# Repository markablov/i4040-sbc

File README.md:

# i4040-sbc
Single-board computer design for Intel 4040 CPU

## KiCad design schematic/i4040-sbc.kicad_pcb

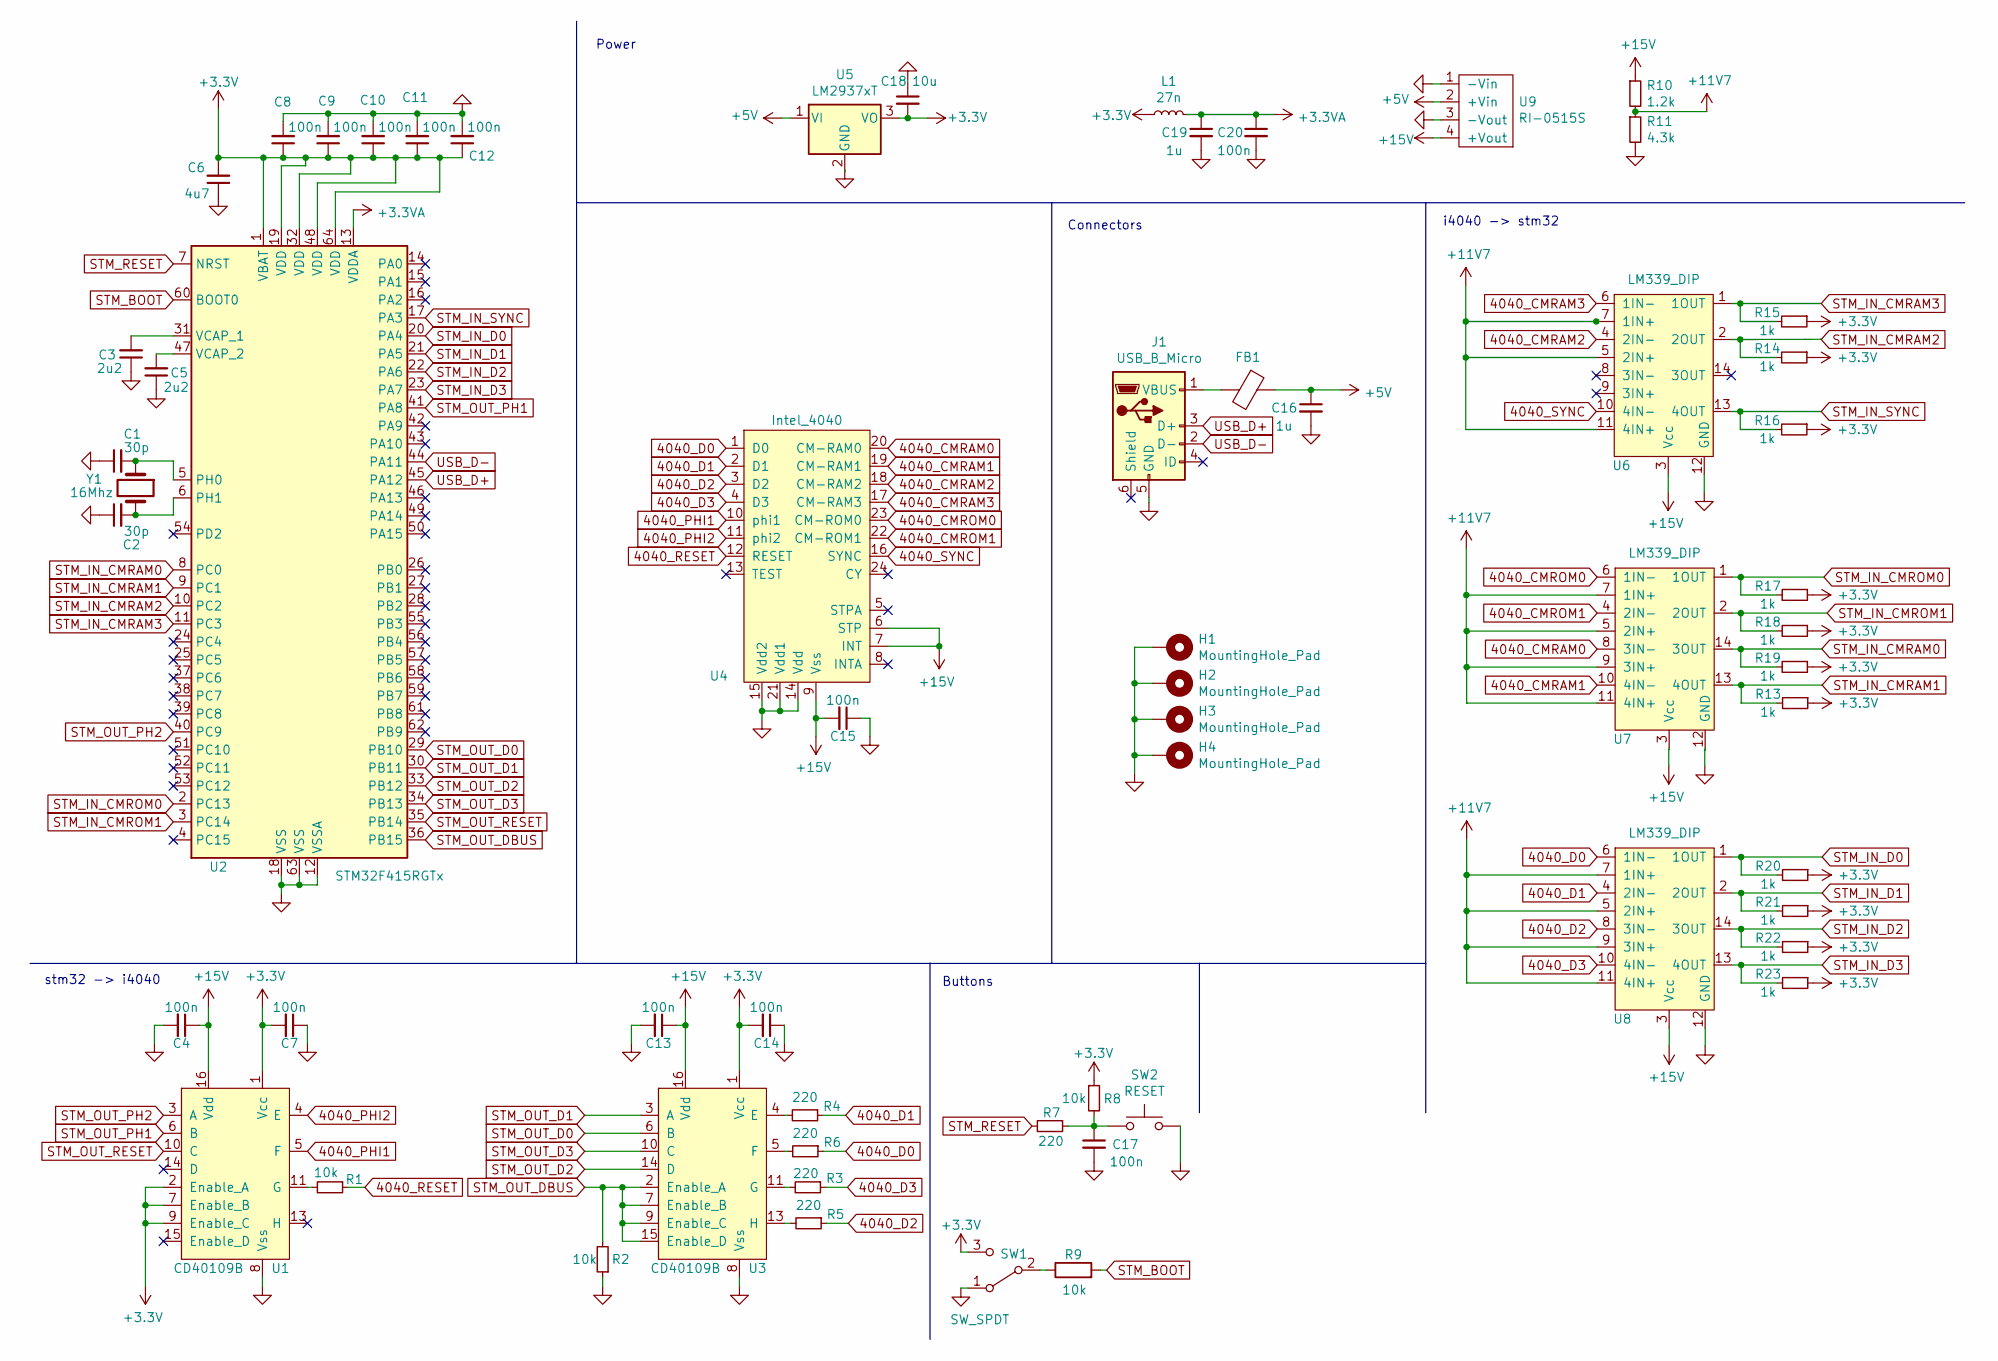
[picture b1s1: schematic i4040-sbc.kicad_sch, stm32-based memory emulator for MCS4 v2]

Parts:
C1, C2: 30p; C_Pillow_L5.6mm_W4mm_D5.6mm_P5.00mm
C3, C5: 2u2; C_Disc_D4.3mm_W1.9mm_P5.00mm
C4, C7, C13, C14, C15, C17, C20: 100n; C_Disc_D7mm_W5mm_P4.00mm
C6: 4u7; C_Disc_D4.3mm_W1.9mm_P5.00mm
C8, C9, C10, C11, C12: 100n; C_Disc_D4.7mm_W2.5mm_P5.00mm
C16, C19: 1u; C_Disc_D4.3mm_W1.9mm_P5.00mm
C18: 10u; C_Disc_D4.7mm_W2.5mm_P5.00mm
FB1: Ferrite_Bead; L_0402_1005Metric_Pad0.77x0.64mm_HandSolder
H1, H2, H3, H4: MountingHole_Pad; MountingHole_2.2mm_M2_Pad
J1: USB_B_Micro; USB_Micro-B_Amphenol_10104110_Horizontal
L1: 27n; L_0402_1005Metric_Pad0.77x0.64mm_HandSolder
R1, R2, R8, R9: 10k; R_Axial_DIN0207_L6.3mm_D2.5mm_P10.16mm_Horizontal
R3, R4, R5, R6, R7: 220; R_Axial_DIN0207_L6.3mm_D2.5mm_P10.16mm_Horizontal
R10: 1.2k; R_Axial_DIN0207_L6.3mm_D2.5mm_P10.16mm_Horizontal
R11: 4.3k; R_Axial_DIN0207_L6.3mm_D2.5mm_P10.16mm_Horizontal
R13, R14, R15, R16, R19, R20, R21, R22, R23: 1k; R_Axial_DIN0207_L6.3mm_D2.5mm_P10.16mm_Horizontal
R17, R18: 1k; R_Axial_DIN0414_L11.9mm_D4.5mm_P15.24mm_Horizontal
SW1: SW_SPDT; SW_Slide_1P2T_CK_OS102011MS2Q
SW2: RESET; SW_Tact_TS3601
U1, U3: CD40109B; SO-16_5.3x10.2mm_P1.27mm
U2: STM32F415RGTx; LQFP-64_10x10mm_P0.5mm
U4: Intel_4040; DIP-24_W15.24mm_Socket
U5: LM2937xT; TO-220-3_Vertical
U6, U7, U8: LM339_DIP; DIP-14_W7.62mm_Socket
U9: RI-0515S; Converter_DCDC_RECOM_R-78S-0.1_THT
Y1: 16Mhz; Crystal_HC49-U_Vertical

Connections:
4040_CMRAM0: U4.20 (CM-RAM0), U7.8 (3IN-)
4040_CMRAM1: U4.19 (CM-RAM1), U7.10 (4IN-)
4040_CMRAM2: U4.18 (CM-RAM2), U6.4 (2IN-)
4040_CMRAM3: U4.17 (CM-RAM3), U6.6 (1IN-)
4040_CMROM0: U4.23 (CM-ROM0), U7.6 (1IN-)
4040_CMROM1: U4.22 (CM-ROM1), U7.4 (2IN-)
4040_D0: R6.1, U4.1 (D0), U8.6 (1IN-)
4040_D1: R4.1, U4.2 (D1), U8.4 (2IN-)
4040_D2: R5.1, U4.3 (D2), U8.8 (3IN-)
4040_D3: R3.1, U4.4 (D3), U8.10 (4IN-)
4040_PHI1: U1.5 (F), U4.10 (phi1)
4040_PHI2: U1.4 (E), U4.11 (phi2)
4040_RESET: R1.1, U4.12 (RESET)
4040_SYNC: U4.16 (SYNC), U6.10 (4IN-)
+3.3VA: C19.1, C20.1, L1.2, U2.13 (VDDA)
+3V3: C6.2, C7.2, C8.1, C9.1, C10.1, C11.1, C12.1, C14.2, C18.2, L1.1, R8.1, R13.1, R14.1, R15.1, R16.1, R17.1, R18.1, R19.1, R20.1, R21.1, R22.1, R23.1, SW1.3 (C), U1.1 (Vcc), U1.2 (Enable_A), U1.7 (Enable_B), U1.9 (Enable_C), U2.1 (VBAT), U2.19 (VDD), U2.32 (VDD), U2.48 (VDD), U2.64 (VDD), U3.1 (Vcc), U5.3 (VO)
+5V: C16.1, FB1.1, U5.1 (VI), U9.2 (+Vin)
+11V7: R10.2, R11.1, U6.5 (2IN+), U6.7 (1IN+), U6.11 (4IN+), U7.5 (2IN+), U7.7 (1IN+), U7.9 (3IN+), U7.11 (4IN+), U8.5 (2IN+), U8.7 (1IN+), U8.9 (3IN+), U8.11 (4IN+)
+15V: C4.1, C13.1, C15.2, R10.1, U1.16 (Vdd), U3.16 (Vdd), U4.6 (STP), U4.7 (INT), U4.9 (Vss), U6.3 (Vcc), U7.3 (Vcc), U8.3 (Vcc), U9.4 (+Vout)
GND: C1.1, C2.1, C3.1, C4.2, C5.1, C6.1, C7.1, C8.2, C9.2, C10.2, C11.2, C12.2, C13.2, C14.1, C15.1, C16.2, C17.2, C18.1, C19.2, C20.2, H1.1, H2.1, H3.1, H4.1, J1.5 (GND), R2.1, R11.2, SW1.1 (A), SW2.2, U1.8 (Vss), U2.12 (VSSA), U2.18 (VSS), U2.63 (VSS), U3.8 (Vss), U4.14 (Vdd), U4.15 (Vdd2), U4.21 (Vdd1), U5.2 (GND), U6.12 (GND), U7.12 (GND), U8.12 (GND), U9.1 (-Vin), U9.3 (-Vout)
unnamed: C17.1, R7.1, R8.2, SW2.1
unnamed: FB1.2, J1.1 (VBUS)
unnamed: R9.1, SW1.2 (B)
unnamed: R1.2, U1.11 (G)
unnamed: C1.2, U2.5 (PH0), Y1.1
unnamed: C2.2, U2.6 (PH1), Y1.2
unnamed: C3.2, U2.31 (VCAP_1)
unnamed: C5.2, U2.47 (VCAP_2)
unnamed: R4.2, U3.4 (E)
unnamed: R6.2, U3.5 (F)
unnamed: R3.2, U3.11 (G)
unnamed: R5.2, U3.13 (H)
STM_BOOT: R9.2, U2.60 (BOOT0)
STM_IN_CMRAM0: R19.2, U2.8 (PC0), U7.14 (3OUT)
STM_IN_CMRAM1: R13.2, U2.9 (PC1), U7.13 (4OUT)
STM_IN_CMRAM2: R14.2, U2.10 (PC2), U6.2 (2OUT)
STM_IN_CMRAM3: R15.2, U2.11 (PC3), U6.1 (1OUT)
STM_IN_CMROM0: R17.2, U2.2 (PC13), U7.1 (1OUT)
STM_IN_CMROM1: R18.2, U2.3 (PC14), U7.2 (2OUT)
STM_IN_D0: R20.2, U2.20 (PA4), U8.1 (1OUT)
STM_IN_D1: R21.2, U2.21 (PA5), U8.2 (2OUT)
STM_IN_D2: R22.2, U2.22 (PA6), U8.14 (3OUT)
STM_IN_D3: R23.2, U2.23 (PA7), U8.13 (4OUT)
STM_IN_SYNC: R16.2, U2.17 (PA3), U6.13 (4OUT)
STM_OUT_D0: U2.29 (PB10), U3.6 (B)
STM_OUT_D1: U2.30 (PB11), U3.3 (A)
STM_OUT_D2: U2.33 (PB12), U3.14 (D)
STM_OUT_D3: U2.34 (PB13), U3.10 (C)
STM_OUT_DBUS: R2.2, U2.36 (PB15), U3.2 (Enable_A), U3.7 (Enable_B), U3.9 (Enable_C), U3.15 (Enable_D)
STM_OUT_PH1: U1.6 (B), U2.41 (PA8)
STM_OUT_PH2: U1.3 (A), U2.40 (PC9)
STM_OUT_RESET: U1.10 (C), U2.35 (PB14)
STM_RESET: R7.2, U2.7 (NRST)
USB_D+: J1.3 (D+), U2.45 (PA12)
USB_D-: J1.2 (D-), U2.44 (PA11)

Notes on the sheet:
Buttons
Connectors
stm32 -> i4040
Power
i4040 -> stm32

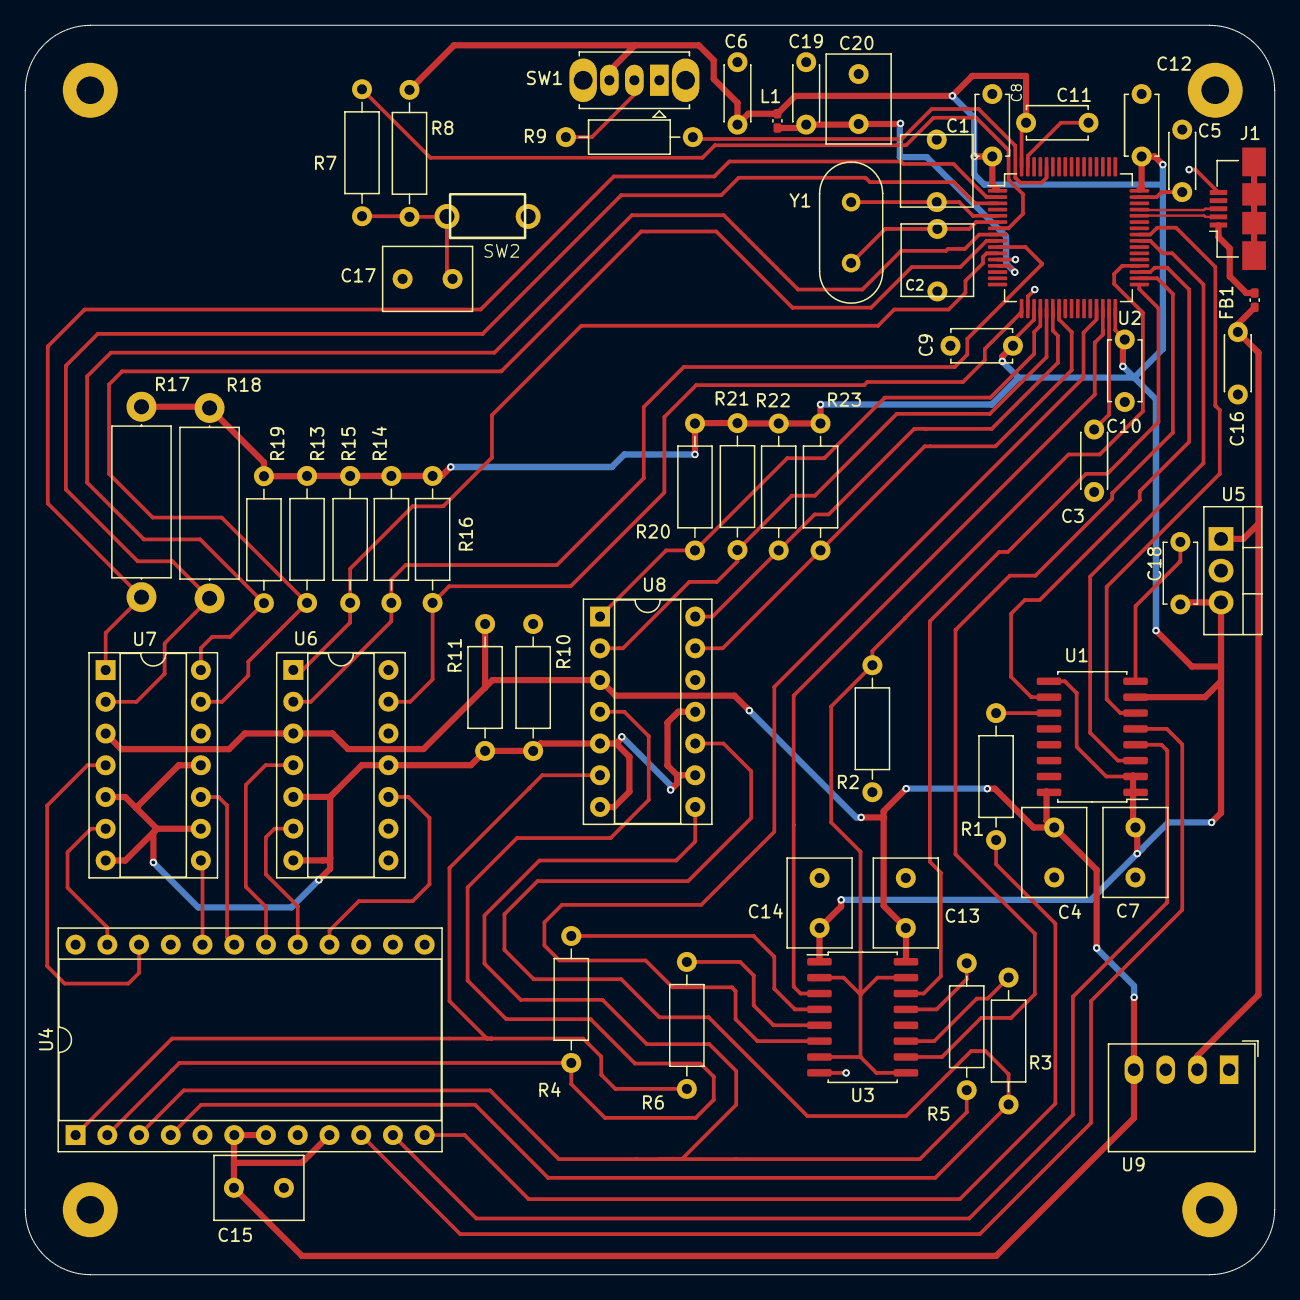
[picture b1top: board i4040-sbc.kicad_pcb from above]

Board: 2 copper layers, 100.0 x 100.0 mm, 61 parts (0 on the bottom side), 55 nets.

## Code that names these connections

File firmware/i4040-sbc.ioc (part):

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Mcu.Name=STM32F415RGTx
Mcu.Package=LQFP64
Mcu.UserName=STM32F415RGTx
PA0-WKUP.GPIOParameters=GPIO_Label
PA0-WKUP.GPIO_Label=OUT_LED
PA0-WKUP.Signal=GPIO_Output
PA11.Mode=Device_Only
PA11.Signal=USB_OTG_FS_DM
PA12.Mode=Device_Only
PA12.Signal=USB_OTG_FS_DP
PA13.Mode=Trace_Asynchronous_SW
PA13.Signal=SYS_JTMS-SWDIO
PA14.Mode=Trace_Asynchronous_SW
PA14.Signal=SYS_JTCK-SWCLK
PA3.GPIOParameters=GPIO_Label
PA3.GPIO_Label=IN_4040_SYNC
PA3.Signal=GPIO_Input
PA4.GPIOParameters=GPIO_Label
PA4.GPIO_Label=IN_4040_D0
PA4.Signal=GPIO_Input
PA5.GPIOParameters=GPIO_Label
PA5.GPIO_Label=IN_4040_D1
PA5.Signal=GPIO_Input
PA6.GPIOParameters=GPIO_Label
PA6.GPIO_Label=IN_4040_D2
PA6.Signal=GPIO_Input
PA7.GPIOParameters=GPIO_Label
PA7.GPIO_Label=IN_4040_D3
PA7.Signal=GPIO_Input
PA8.GPIOParameters=GPIO_Label
PA8.GPIO_Label=OUT_4040_PHI1
PA8.Signal=S_TIM1_CH1
PB1.GPIOParameters=GPIO_Label
PB1.GPIO_Label=OUT_TEST1
PB1.Signal=GPIO_Output
PB10.GPIOParameters=GPIO_Label
PB10.GPIO_Label=OUT_4040_D0
PB10.Signal=GPIO_Output
PB11.GPIOParameters=GPIO_Label
PB11.GPIO_Label=OUT_4040_D1
PB11.Signal=GPIO_Output
PB12.GPIOParameters=GPIO_Label
PB12.GPIO_Label=OUT_4040_D2
PB12.Signal=GPIO_Output
PB13.GPIOParameters=GPIO_Label
PB13.GPIO_Label=OUT_4040_D3
PB13.Signal=GPIO_Output
PB14.GPIOParameters=GPIO_Label
PB14.GPIO_Label=OUT_4040_RESET
PB14.Signal=GPIO_Output
PB15.GPIOParameters=GPIO_Label
PB15.GPIO_Label=OUT_4040_DBUS
PB15.Signal=GPIO_Output
PB3.Mode=Trace_Asynchronous_SW
PB3.Signal=SYS_JTDO-SWO
PC0.GPIOParameters=GPIO_Label
PC0.GPIO_Label=IN_4040_CMRAM0
PC0.Signal=GPIO_Input
PC1.GPIOParameters=GPIO_Label
PC1.GPIO_Label=IN_4040_CMRAM1
PC1.Signal=GPIO_Input
PC13-ANTI_TAMP.GPIOParameters=GPIO_Label
PC13-ANTI_TAMP.GPIO_Label=IN_4040_CMROM0
PC13-ANTI_TAMP.Signal=GPIO_Input
PC14-OSC32_IN.GPIOParameters=GPIO_Label
PC14-OSC32_IN.GPIO_Label=IN_4040_CMROM1
PC14-OSC32_IN.Signal=GPIO_Input
PC2.GPIOParameters=GPIO_Label
PC2.GPIO_Label=IN_4040_CMRAM2
PC2.Signal=GPIO_Input
PC3.GPIOParameters=GPIO_Label
PC3.GPIO_Label=IN_4040_CMRAM3
PC3.Signal=GPIO_Input
PC5.GPIOParameters=GPIO_Label
PC5.GPIO_Label=OUT_TEST0
PC5.Signal=GPIO_Output
PC9.GPIOParameters=GPIO_Label
PC9.GPIO_Label=OUT_4040_PHI2
PC9.Signal=S_TIM8_CH4
PH0-OSC_IN.Mode=HSE-External-Oscillator
PH0-OSC_IN.Signal=RCC_OSC_IN
PH1-OSC_OUT.Mode=HSE-External-Oscillator
PH1-OSC_OUT.Signal=RCC_OSC_OUT
RCC.HSE_VALUE=16000000
RCC.SYSCLKFreq_VALUE=168000000
RCC.SYSCLKSource=RCC_SYSCLKSOURCE_PLLCLK
board=custom

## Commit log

2023-11-03 Initial design
